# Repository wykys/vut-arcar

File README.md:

# VUT UREL Autonomous Racing Car

Main board photo.

## Bluetooth GATT
```
# UUID service:  
49535343-FE7D-4AE5-8FA9-9FAFD205E455  
# UUID write charasteristic
49535343-8841-43F4-A8D4-ECBE34729BB3  
# UUID read charasteristic
49535343-1E4D-4BD9-BA61-23C647249616  
```

configuration [Serial-Bluetooth](https://play.google.com/store/apps/details?id=de.kai_morich.serial_bluetooth_terminal&hl=cs)

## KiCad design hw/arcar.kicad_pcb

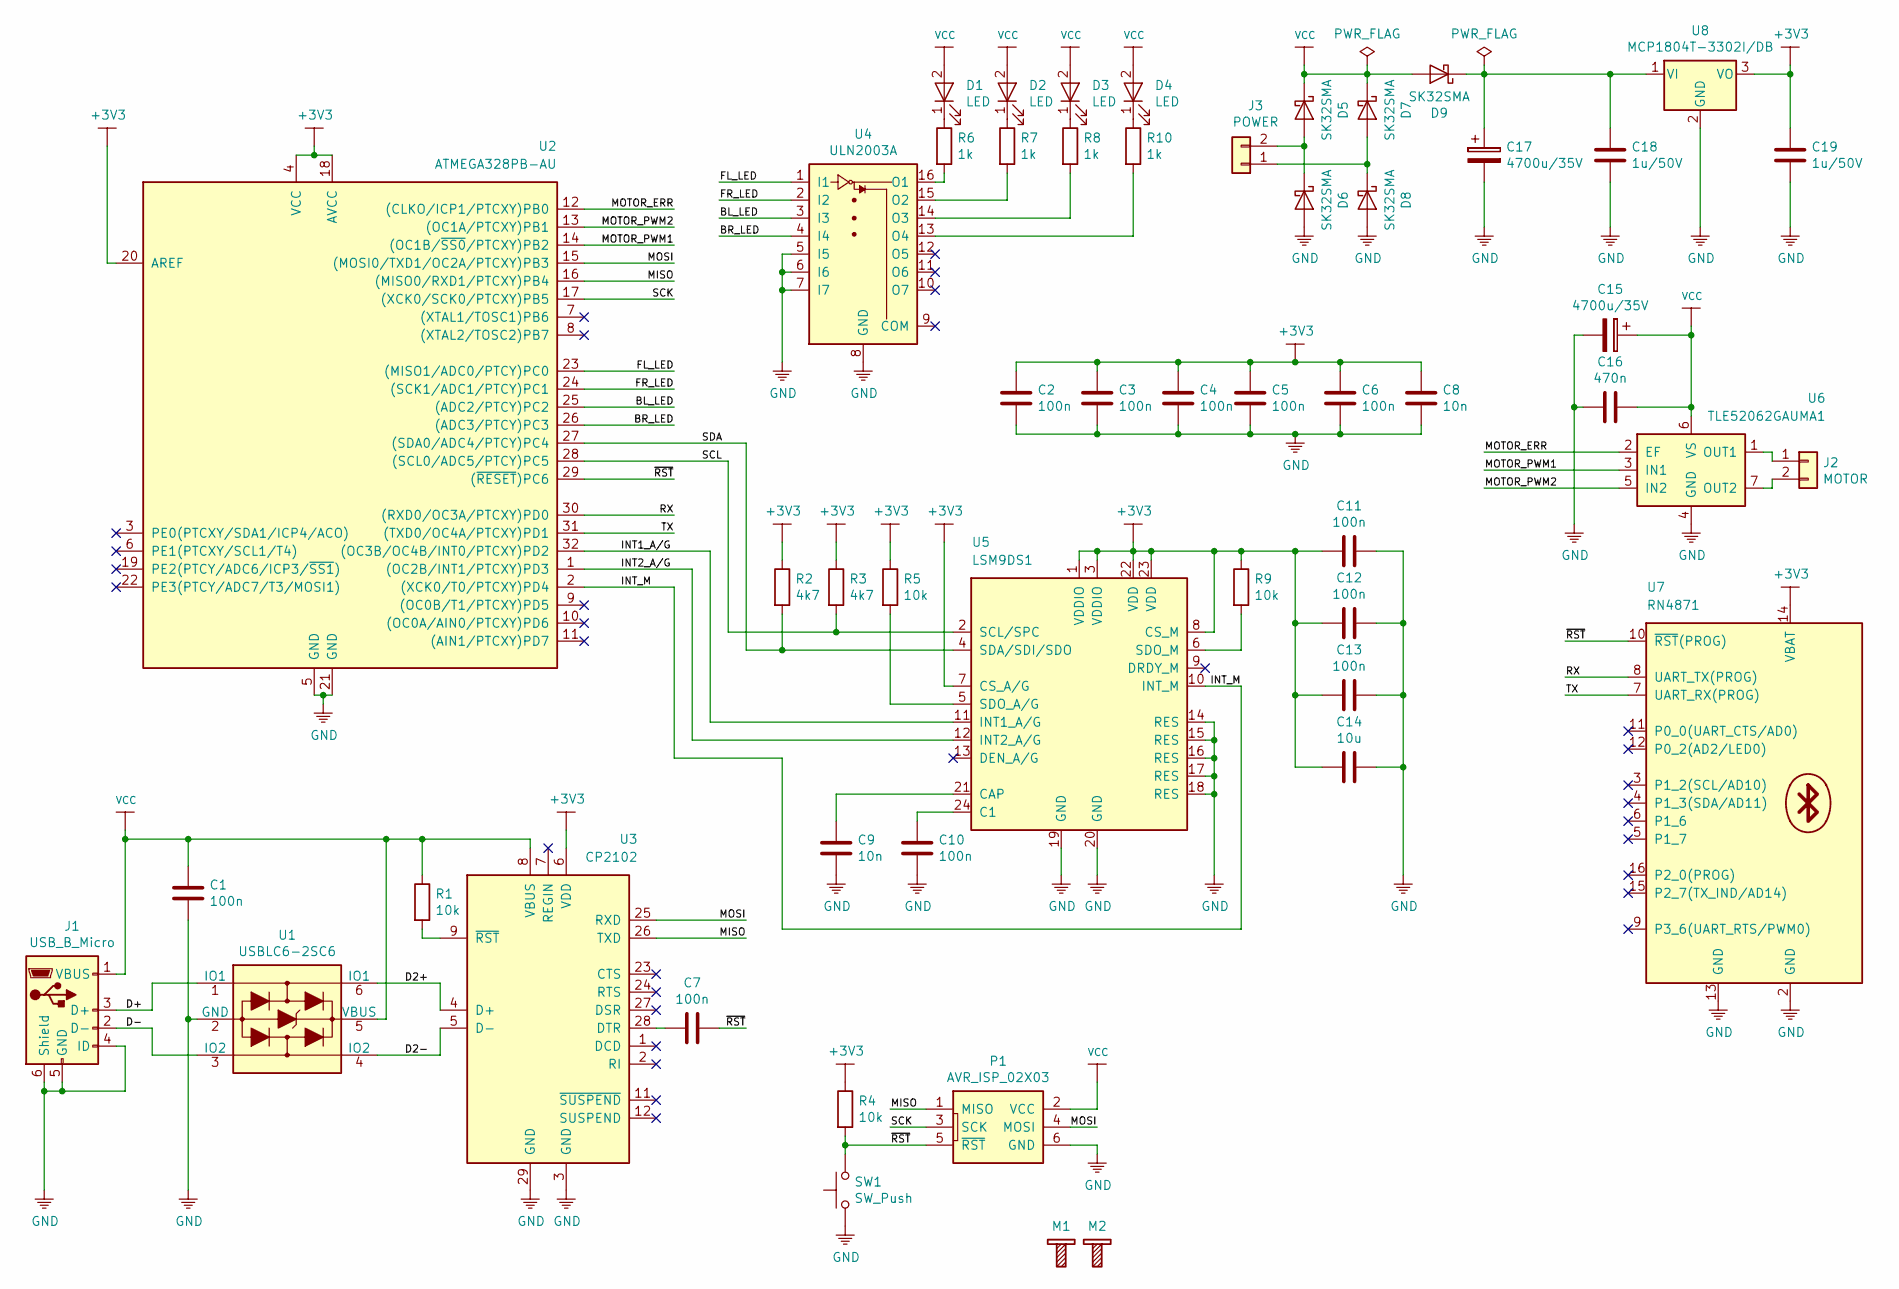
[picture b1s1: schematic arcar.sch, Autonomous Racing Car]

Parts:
C1, C2, C3, C4, C5, C6, C7, C10, C11, C12, C13: 100n; C_0805_HandSoldering
C8, C9: 10n; C_0805_HandSoldering
C14: 10u; C_0805_HandSoldering
C15, C17: 4700u/35V; CP_Radial_D4.0mm_P1.50mm
C16: 470n; C_0805_HandSoldering
C18, C19: 1u/50V; C_0805_HandSoldering
D1, D2, D3, D4: LED; Pin_Header_Straight_1x02_Pitch2.54mm
D5, D6, D7, D8, D9: SK32SMA; D_SMA
J1: USB_B_Micro; USB_Micro-B_Wuerth-614105150721_Vertical_CircularHoles
J2: MOTOR; Pin_Header_Straight_1x02_Pitch2.54mm
J3: POWER; Pin_Header_Straight_1x02_Pitch2.54mm
M1, M2: screw; screw_M3
P1: AVR_ISP_02X03; IDC_Header_Straight_6pins
R1, R4, R5, R9: 10k; R_0805_HandSoldering
R2, R3: 4k7; R_0805_HandSoldering
R6, R7, R8, R10: 1k; R_0805_HandSoldering
SW1: SW_Push; SW_PUSH_6mm_h5mm
U1: USBLC6-2SC6; SOT-23-6
U2: ATMEGA328PB-AU; TQFP-32_7x7mm_Pitch0.8mm
U3: CP2102; QFN-28-1EP_5x5mm_Pitch0.5mm
U4: ULN2003A; SOIC-16_3.9x9.9mm_Pitch1.27mm
U5: LSM9DS1; LGA-24L_3x3.5mm_Pitch0.43mm
U6: TLE52062GAUMA1; TO-263-7_TabPin4
U7: RN4871
U8: MCP1804T-3302I/DB; SOT-223-3_TabPin2

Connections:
+3V3: C2.1, C3.1, C4.1, C5.1, C6.1, C8.1, C11.2, C12.2, C13.2, C14.2, C19.1, R2.1, R3.1, R4.1, R5.1, R9.1, U2.4 (VCC), U2.18 (AVCC), U2.20 (AREF), U3.6 (VDD), U5.1 (VDDIO), U5.3 (VDDIO), U5.7 (CS_A/G), U5.8 (CS_M), U5.22 (VDD), U5.23 (VDD), U7.14 (VBAT), U8.3 (VO)
/BL_LED: U2.25 ((ADC2/PTCY)PC2), U4.3 (I3)
/BR_LED: U2.26 ((ADC3/PTCY)PC3), U4.4 (I4)
/D2+: U1.6 (IO1), U3.4 (D+)
/D2-: U1.4 (IO2), U3.5 (D-)
/D+: J1.3 (D+), U1.1 (IO1)
/D-: J1.2 (D-), U1.3 (IO2)
/FL_LED: U2.23 ((MISO1/ADC0/PTCY)PC0), U4.1 (I1)
/FR_LED: U2.24 ((SCK1/ADC1/PTCY)PC1), U4.2 (I2)
/INT1_A/G: U2.32 ((OC3B/OC4B/INT0/PTCXY)PD2), U5.11 (INT1_A/G)
/INT2_A/G: U2.1 ((OC2B/INT1/PTCXY)PD3), U5.12 (INT2_A/G)
/INT_M: U2.2 ((XCK0/T0/PTCXY)PD4), U5.10 (INT_M)
/MISO: P1.1 (MISO), U2.16 ((MISO0/RXD1/PTCXY)PB4), U3.26 (TXD)
/MOSI: P1.4 (MOSI), U2.15 ((MOSI0/TXD1/OC2A/PTCXY)PB3), U3.25 (RXD)
/MOTOR_ERR: U2.12 ((CLKO/ICP1/PTCXY)PB0), U6.2 (EF)
/MOTOR_PWM1: U2.14 ((OC1B/~SS0~/PTCXY)PB2), U6.3 (IN1)
/MOTOR_PWM2: U2.13 ((OC1A/PTCXY)PB1), U6.5 (IN2)
/RX: U2.30 ((RXD0/OC3A/PTCXY)PD0), U7.8 (UART_TX(PROG))
/SCK: P1.3 (SCK), U2.17 ((XCK0/SCK0/PTCXY)PB5)
/SCL: R3.2, U2.28 ((SCL0/ADC5/PTCY)PC5), U5.2 (SCL/SPC)
/SDA: R2.2, U2.27 ((SDA0/ADC4/PTCY)PC4), U5.4 (SDA/SDI/SDO)
/TX: U2.31 ((TXD0/OC4A/PTCXY)PD1), U7.7 (UART_RX(PROG))
/~RST: C7.1, P1.5 (~RST), R4.2, SW1.2, U2.29 ((~RESET~)PC6), U7.10 (~RST~(PROG))
GND: C1.2, C2.2, C3.2, C4.2, C5.2, C6.2, C8.2, C9.2, C10.2, C11.1, C12.1, C13.1, C14.1, C15.2, C16.2, C17.2, C18.2, C19.2, D6.2 (A), D8.2 (A), J1.4 (ID), J1.5 (GND), J1.6 (Shield), P1.6 (GND), SW1.1, U1.2 (GND), U2.5 (GND), U2.21 (GND), U3.3 (GND), U3.29 (GND), U4.5 (I5), U4.6 (I6), U4.7 (I7), U4.8 (GND), U5.14 (RES), U5.15 (RES), U5.16 (RES), U5.17 (RES), U5.18 (RES), U5.19 (GND), U5.20 (GND), U6.4 (GND), U7.2 (GND), U7.13 (GND), U8.2 (GND)
unnamed: C7.2, U3.28 (DTR)
unnamed: C9.1, U5.21 (CAP)
unnamed: C10.1, U5.24 (C1)
unnamed: C17.1, C18.1, D9.1 (K), U8.1 (VI)
unnamed: D1.1 (K), R6.1
unnamed: D2.1 (K), R7.1
unnamed: D3.1 (K), R8.1
unnamed: D4.1 (K), R10.1
unnamed: D5.2 (A), D6.1 (K), J3.2
unnamed: D7.2 (A), D8.1 (K), J3.1
unnamed: J2.1, U6.1 (OUT1)
unnamed: J2.2, U6.7 (OUT2)
unnamed: R1.2, U3.9 (~RST)
unnamed: R5.2, U5.5 (SDO_A/G)
unnamed: R6.2, U4.16 (O1)
unnamed: R7.2, U4.15 (O2)
unnamed: R8.2, U4.14 (O3)
unnamed: R9.2, U5.6 (SDO_M)
unnamed: R10.2, U4.13 (O4)
VCC: C1.1, C15.1, C16.1, D1.2 (A), D2.2 (A), D3.2 (A), D4.2 (A), D5.1 (K), D7.1 (K), D9.2 (A), J1.1 (VBUS), P1.2 (VCC), R1.1, U1.5 (VBUS), U3.8 (VBUS), U6.6 (VS)

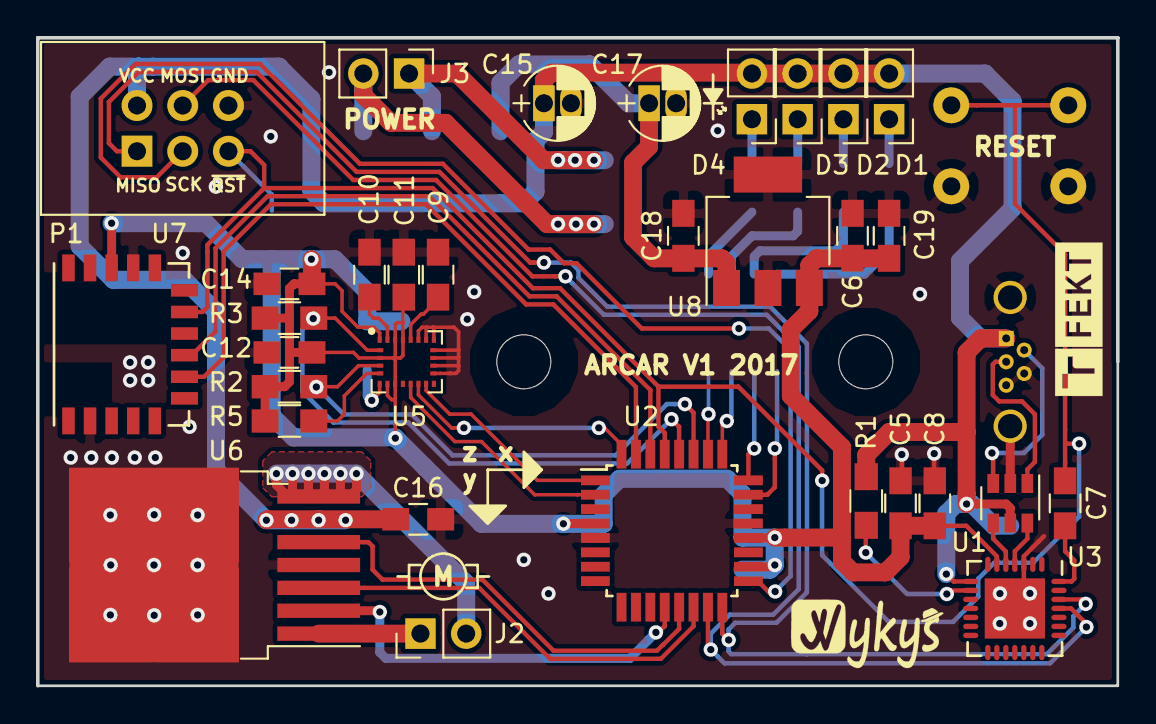
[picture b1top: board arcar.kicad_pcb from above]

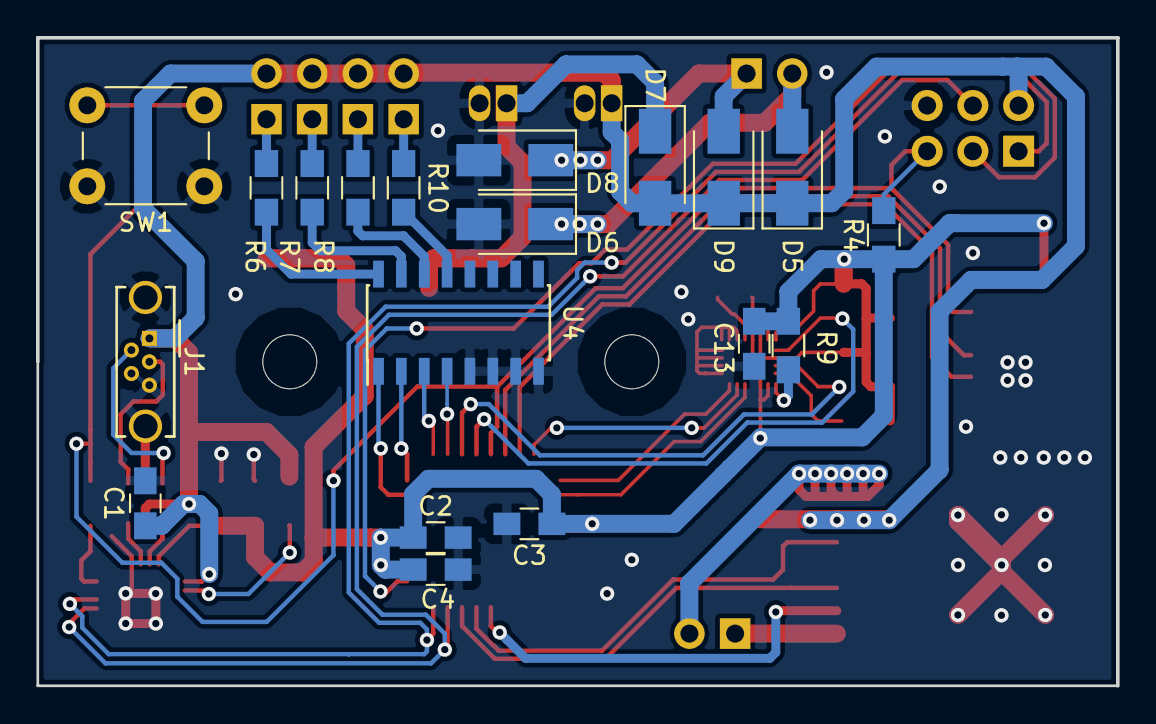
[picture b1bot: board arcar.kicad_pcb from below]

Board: 2 copper layers, 60.0 x 36.0 mm, 53 parts (19 on the bottom side), 44 nets.

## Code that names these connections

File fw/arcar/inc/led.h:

/*
·* LED driver
·*
·* autor: wykys
·* verze: 1.0
·* datum: 2.11.2017
·*/

#ifndef WYK_LED_H_INCLUDED
#define WYK_LED_H_INCLUDED

#include "settings.h"
#include <avr/io.h>

#define LED_FRONT_LEFT_PIN   (1<<PC0)
#define LED_FRONT_RIGHT_PIN  (1<<PC1)
#define LED_BACK_LEFT_PIN    (1<<PC2)
#define LED_BACK_RIGHT_PIN   (1<<PC3)

#define LED_DDR   DDRC
#define LED_PIN   PINC
#define LED_PORT  PORTC

#define LED_ON  true
#define LED_OFF false

// ========================================================
class LED
{
public:
    LED();
    void forward_left(bool state);
    void forward_right(bool state);
    void reverse_left(bool state);
    void reverse_right(bool state);
};
// ========================================================

#endif // WYK_LED_H_INCLUDED

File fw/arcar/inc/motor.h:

/*
 * library for work with motor
 *
 * autor: wykys
 * verze: 1.0
 * datum: 5.12.2017
 */

#ifndef WYK_MOTOR_H_INCLUDED
#define WYK_MOTOR_H_INCLUDED

#include "settings.h"
#include <avr/io.h>
#include <util/delay.h>

#define MOTOR_ERR_PIN  (1<<PB0)
#define MOTOR_DIR_PIN  (1<<PB1)
#define MOTOR_PWM_PIN  (1<<PB2)

#define MOTOR_DDR   DDRB
#define MOTOR_PIN   PINB
#define MOTOR_PORT  PORTB

#define MOTOR_TIMER_TOP 255

#define MOTOR_DIRECTION_FORVARD true
#define MOTOR_DIRECTION_REVERS  false

// ========================================================
class Motor
{
public:
    Motor(uint8_t power=0, bool directon=MOTOR_DIRECTION_FORVARD);
    void forward(uint8_t power);
    void reverse(uint8_t power);
    void stop();
    void fast_stop();
    uint8_t get_power();
    bool get_directon();
private:
    bool direction;
    uint8_t power;
};
// ========================================================

#endif // WYK_MOTOR_H_INCLUDED

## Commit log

2017-10-29 added datasheets ATmega328P and RN4871
2017-10-29 added hw .gitignore
2017-10-29 added schematic preview
2017-10-30 added pdf schematic
2017-10-30 added ATmega328PB datasheet
2017-11-01 updated schematic, change microcontoler to ATmega328PB and added H bridge, MPU-6050, USB to UART converter and power source
2017-11-01 updated schematic, chnde ISP VCC conection before LDO
2017-11-06 updated schematic
2017-11-06 assigned footprints
2017-11-06 added board
2017-11-07 reduced schematic
2017-11-07 added LSM9DS1 datasheet
2017-11-07 added CP2102 datasheet
2017-11-07 big reduced change all power source
2017-11-07 added 3D
2017-11-07 all the components are placed on the board
2017-11-07 all routed
2017-11-07 PCB upgraded
2017-11-07 board updated
2017-11-07 added wykys logo
2017-11-08 top img updated
2017-11-08 PCB drill updated
2017-11-08 added grber
2017-11-08 added datasheet TLE5206
2017-11-08 change LED resistors
2017-11-08 added global .gitignore
2017-11-08 added boom
2017-11-09 added bom script and your output
2017-11-09 updated bom script and their outputs
2017-11-09 updated bom script
2017-11-09 added gathema script
2017-11-09 added gathema script output
2017-11-09 added desctiption to bom.py
2017-11-24 added fabrication
2017-11-27 added avr8-gnu-toolchain v3.5.4 x64
2017-11-27 added Atmel Device Family Packs (DFP) v1.2.150
2017-11-27 added fw/.gitignore
2017-11-27 added bootloader edited Optiboot for m328p
2017-11-28 bootloader ported for m328pb
2017-11-28 changed programmer in bootloader
2017-11-28 renamed fw/bootloader/lib to fw/bootloader/inc
2017-12-04 added init commit main firmware ARCAR
2017-12-05 deleted unnecessary files
2017-12-05 fixed i2c header
2017-12-05 fixed motor change direction problem
2017-12-05 updated wyk_stdio.h for print usb and bluetooth
2017-12-06 refactored motor driver
2017-12-06 refactored LED driver
2017-12-06 refactored LSM9DS1
2017-12-06 updated printf float
2017-12-06 updated boletooth wait to buffer in end line
2017-12-06 added asm to make
2017-12-06 refactored I2C
2017-12-14 updated Makefile to relativer paths
2017-12-14 updated LSM9DS1 added default address
2017-12-14 updated bluetooth
2017-12-14 updated main file
2017-12-14 bluetooth refactored
2017-12-14 usb refactored
2017-12-14 make updated
2017-12-14 added avrdude config for m328pb
2017-12-14 updater readme
2018-11-12 Project converted to AVR-tools
